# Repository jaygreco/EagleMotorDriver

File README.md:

EagleMotorDriver
================

The eagle filesizzles for the motor drizzle.

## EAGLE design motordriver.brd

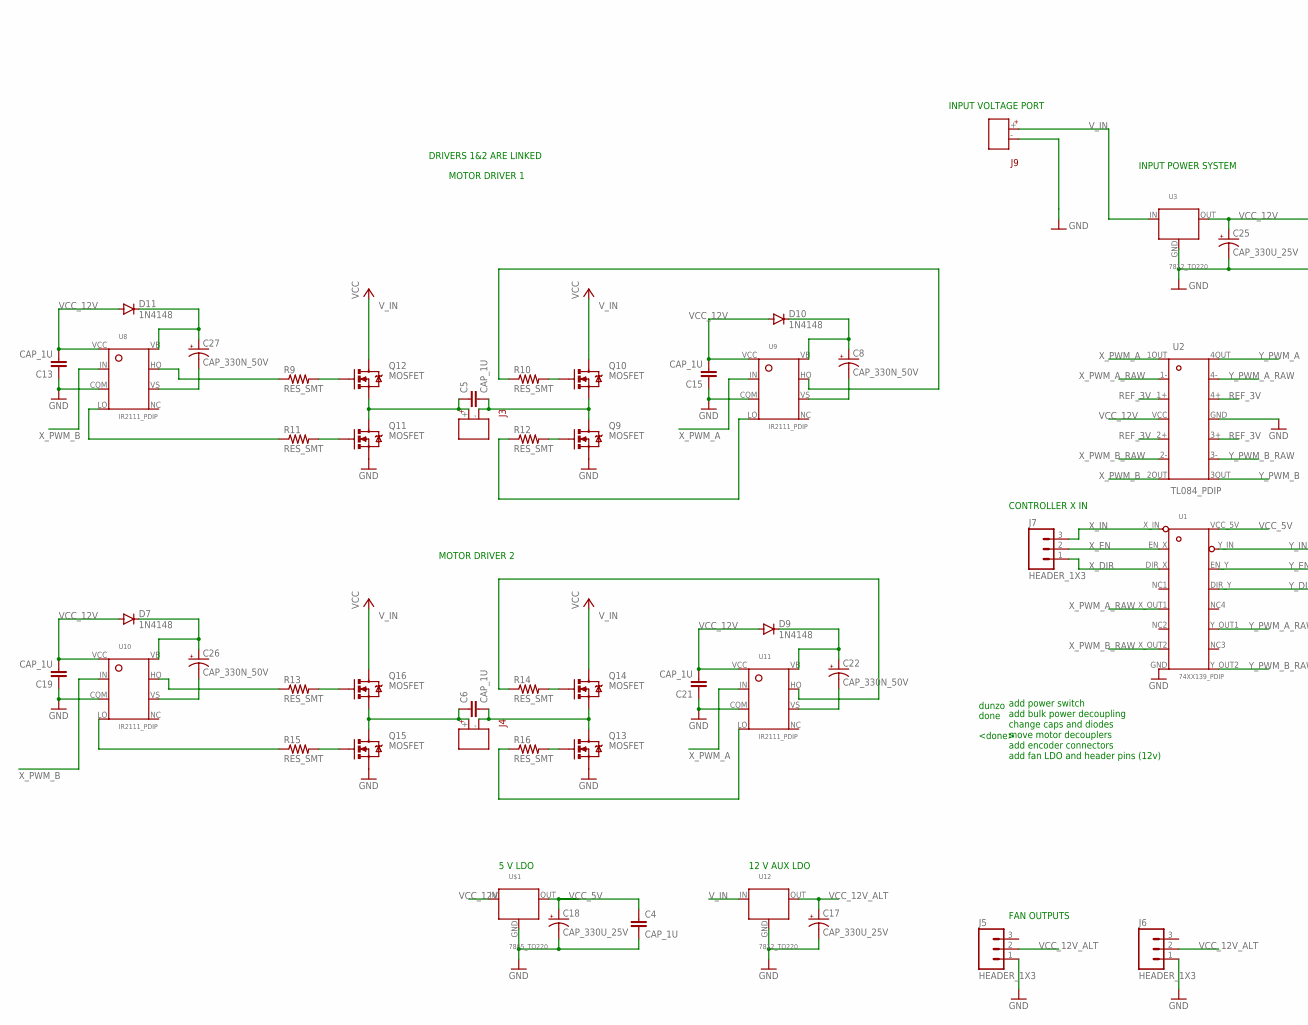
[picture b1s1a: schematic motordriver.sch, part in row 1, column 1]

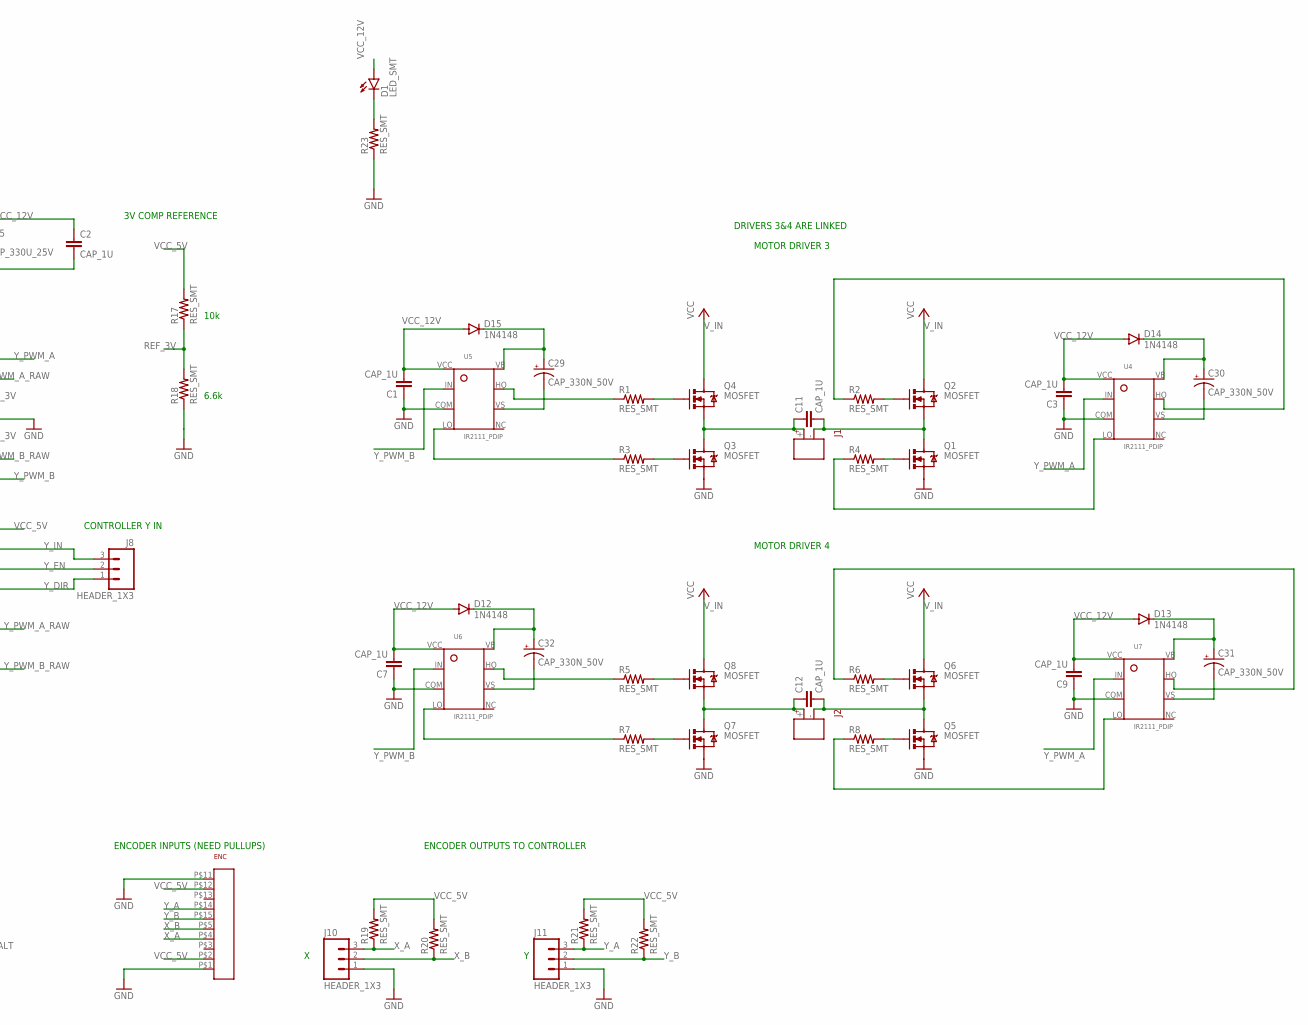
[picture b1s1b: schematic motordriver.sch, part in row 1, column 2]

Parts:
C1, C2, C3, C4, C5, C6, C7, C9, C11, C12, C13, C15, C19, C21: CAP_1U; 2DIP
C8, C22, C26, C27, C29, C30, C31, C32: CAP_330N_50V; RADIAL_5
C17, C18, C25: CAP_330U_25V; RADIAL_1O
D1: LED_SMT; LED_0603
D7, D9, D10, D11, D12, D13, D14, D15: 1N4148
ENC: CONN_5X2
J1, J2, J3, J4, J9: CONNECTOR_MOTORS; CONN_MOTOR
J5, J6, J7, J8, J10, J11: HEADER_1X3
Q1, Q2, Q3, Q4, Q5, Q6, Q7, Q8, Q9, Q10, Q11, Q12, Q13, Q14, Q15, Q16: MOSFET
R1, R2, R3, R4, R5, R6, R7, R8, R9, R10, R11, R12, R13, R14, R15, R16, R17, R18, R19, R20, R21, R22, R23: RES_SMT; 0603
U1: 74XX139_PDIP; 16PDIP
U2: TL084_PDIP; 14PDIP
U3, U12: 7812_TO220; TO-220
U4, U5, U6, U7, U8, U9, U10, U11: IR2111_PDIP; 8PDIP
U$1: 7805_TO220; TO-220

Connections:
GND_32: C1.P$1 (1), C2.P$2 (2), C3.P$1 (1), C4.P$2 (2), C7.P$1 (1), C9.P$1 (1), C13.P$1 (1), C15.P$1 (1), C17.-, C18.-, C19.P$1 (1), C21.P$1 (1), C25.-, ENC.P$1, ENC.P$11, J5.1, J6.1, J9.-, J10.1, J11.1, Q1.S, Q3.S, Q5.S, Q7.S, Q9.S, Q11.S, Q13.S, Q15.S, R18.1, R23.1, U1.GND, U2.GND, U3.GND, U4.COM, U5.COM, U6.COM, U7.COM, U8.COM, U9.COM, U10.COM, U11.COM, U12.GND, U$1.GND
unnamed: R12.1, U9.LO
unnamed: R8.1, U7.LO
unnamed: R10.1, U9.HO
unnamed: D1.C, R23.2
unnamed: R15.1, U10.LO
unnamed: C29.+, D15.C, U5.VB
unnamed: Q1.G, R4.2
unnamed: C29.-, U5.VS
unnamed: R1.1, U5.HO
unnamed: Q4.G, R1.2
unnamed: C11.P$1 (1), J1.+, Q3.D, Q4.S
unnamed: R4.1, U4.LO
unnamed: R3.1, U5.LO
unnamed: C11.P$2 (2), J1.-, Q1.D, Q2.S
unnamed: Q3.G, R3.2
unnamed: Q2.G, R2.2
unnamed: C30.+, D14.C, U4.VB
unnamed: C30.-, U4.VS
unnamed: R2.1, U4.HO
unnamed: R9.1, U8.HO
unnamed: R11.1, U8.LO
unnamed: C32.+, D12.C, U6.VB
unnamed: C32.-, U6.VS
unnamed: R5.1, U6.HO
unnamed: Q8.G, R5.2
unnamed: C12.P$1 (1), J2.+, Q7.D, Q8.S
unnamed: Q5.G, R8.2
unnamed: C12.P$2 (2), J2.-, Q5.D, Q6.S
unnamed: C31.+, D13.C, U7.VB
unnamed: C31.-, U7.VS
unnamed: R6.1, U7.HO
unnamed: R7.1, U6.LO
unnamed: Q7.G, R7.2
unnamed: Q6.G, R6.2
unnamed: R16.1, U11.LO
unnamed: Q13.G, R16.2
unnamed: C27.+, D11.C, U8.VB
unnamed: C27.-, U8.VS
unnamed: Q9.G, R12.2
unnamed: Q12.G, R9.2
unnamed: C5.P$1 (1), J3.+, Q11.D, Q12.S
unnamed: C5.P$2 (2), J3.-, Q9.D, Q10.S
unnamed: C8.+, D10.C, U9.VB
unnamed: C8.-, U9.VS
unnamed: Q11.G, R11.2
unnamed: Q10.G, R10.2
unnamed: C26.+, D7.C, U10.VB
unnamed: C26.-, U10.VS
unnamed: R13.1, U10.HO
unnamed: Q16.G, R13.2
unnamed: C6.P$1 (1), J4.+, Q15.D, Q16.S
unnamed: C6.P$2 (2), J4.-, Q13.D, Q14.S
unnamed: C22.+, D9.C, U11.VB
unnamed: C22.-, U11.VS
unnamed: R14.1, U11.HO
unnamed: Q15.G, R15.2
unnamed: Q14.G, R14.2
REF_3V: R17.1, R18.2, U2.1+, U2.2+, U2.3+, U2.4+
VCC_5V: C4.P$1 (1), C18.+, ENC.P$2, ENC.P$12, R17.2, R19.2, R20.2, R21.2, R22.2, U1.VCC_5V, U$1.OUT
VCC_12V: C1.P$2 (2), C2.P$1 (1), C3.P$2 (2), C7.P$2 (2), C9.P$2 (2), C13.P$2 (2), C15.P$2 (2), C19.P$2 (2), C21.P$2 (2), C25.+, D1.A, D7.A, D9.A, D10.A, D11.A, D12.A, D13.A, D14.A, D15.A, U2.VCC, U3.OUT, U4.VCC, U5.VCC, U6.VCC, U7.VCC, U8.VCC, U9.VCC, U10.VCC, U11.VCC, U$1.IN
VCC_12V_ALT: C17.+, J5.2, J6.2, U12.OUT
V_IN: J9.+, Q2.D, Q4.D, Q6.D, Q8.D, Q10.D, Q12.D, Q14.D, Q16.D, U3.IN, U12.IN
X_A: ENC.P$4, J10.3, R19.1
X_B: ENC.P$5, J10.2, R20.1
X_DIR: J7.1, U1.DIR_X
X_EN: J7.2, U1.EN_X
X_IN: J7.3, U1.X_IN
X_PWM_A: U2.1OUT (OUT1), U9.IN, U11.IN
X_PWM_A_RAW: U1.X_OUT1, U2.1-
X_PWM_B: U2.2OUT (OUT2), U8.IN, U10.IN
X_PWM_B_RAW: U1.X_OUT2, U2.2-
Y_A: ENC.P$14, J11.3, R21.1
Y_B: ENC.P$15, J11.2, R22.1
Y_DIR: J8.1, U1.DIR_Y
Y_EN: J8.2, U1.EN_Y
Y_IN: J8.3, U1.Y_IN
Y_PWM_A: U2.4OUT (OUT4), U4.IN, U7.IN
Y_PWM_A_RAW: U1.Y_OUT1, U2.4-
Y_PWM_B: U2.3OUT (OUT3), U5.IN, U6.IN
Y_PWM_B_RAW: U1.Y_OUT2, U2.3-

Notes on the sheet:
add power switch add bulk power decoupling change caps and diodes move motor decouplers add encoder connectors add fan LDO and header pins (12v)
<done>
dunzo
done
5 V LDO
12 V AUX LDO
CONTROLLER X IN
CONTROLLER Y IN
MOTOR DRIVER 1
MOTOR DRIVER 2
MOTOR DRIVER 3
MOTOR DRIVER 4
ENCODER INPUTS (NEED PULLUPS)
INPUT POWER SYSTEM
3V COMP REFERENCE
DRIVERS 1&2 ARE LINKED
DRIVERS 3&4 ARE LINKED
10k
6.6k
INPUT VOLTAGE PORT
FAN OUTPUTS
ENCODER OUTPUTS TO CONTROLLER

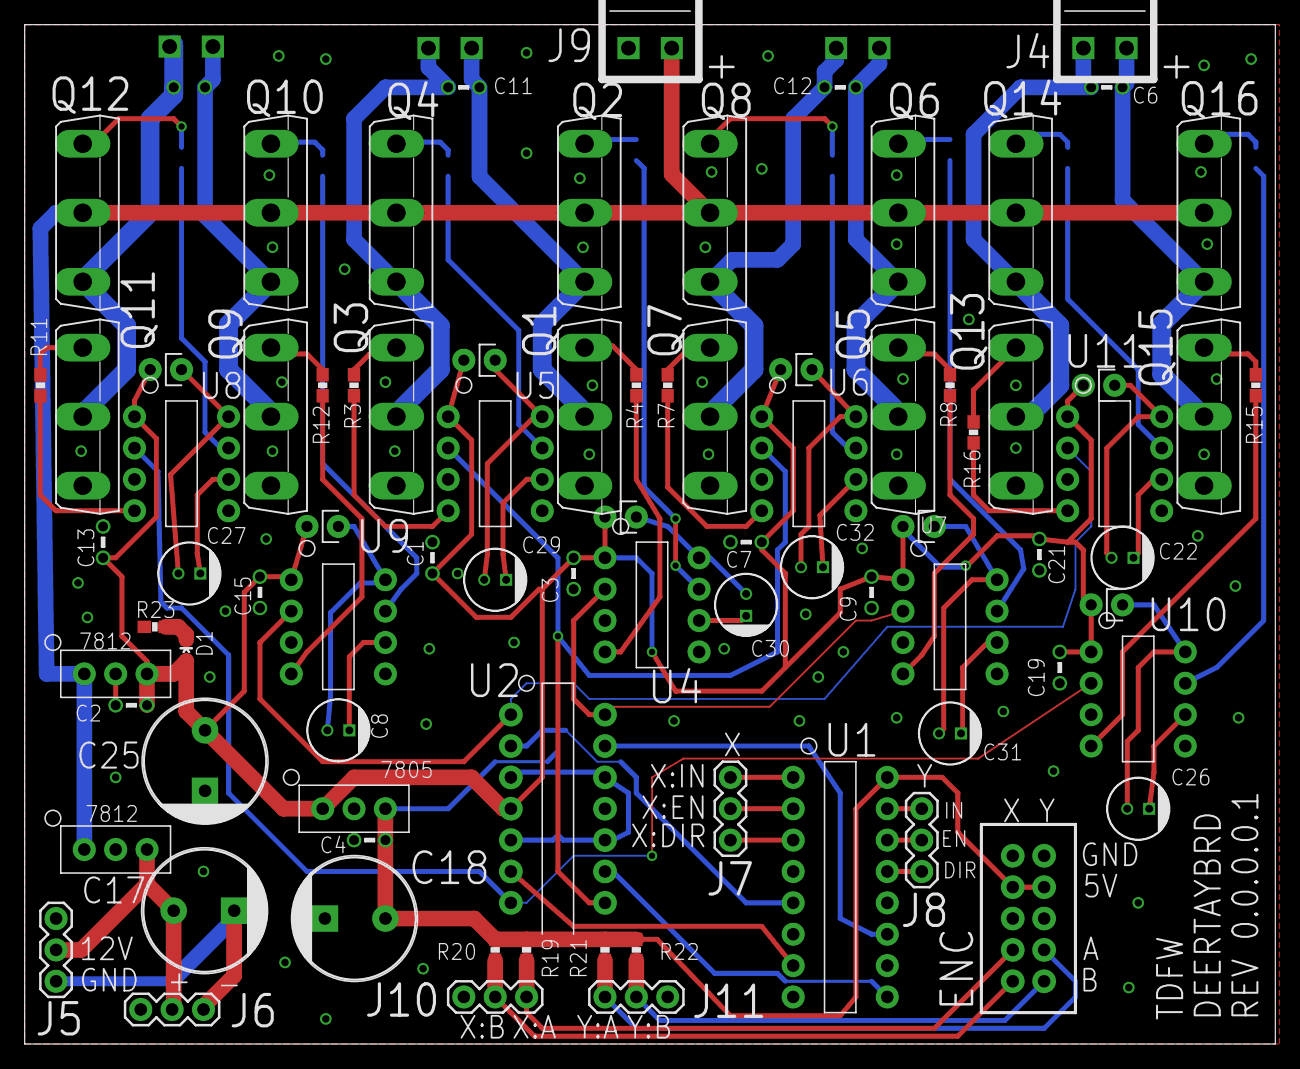
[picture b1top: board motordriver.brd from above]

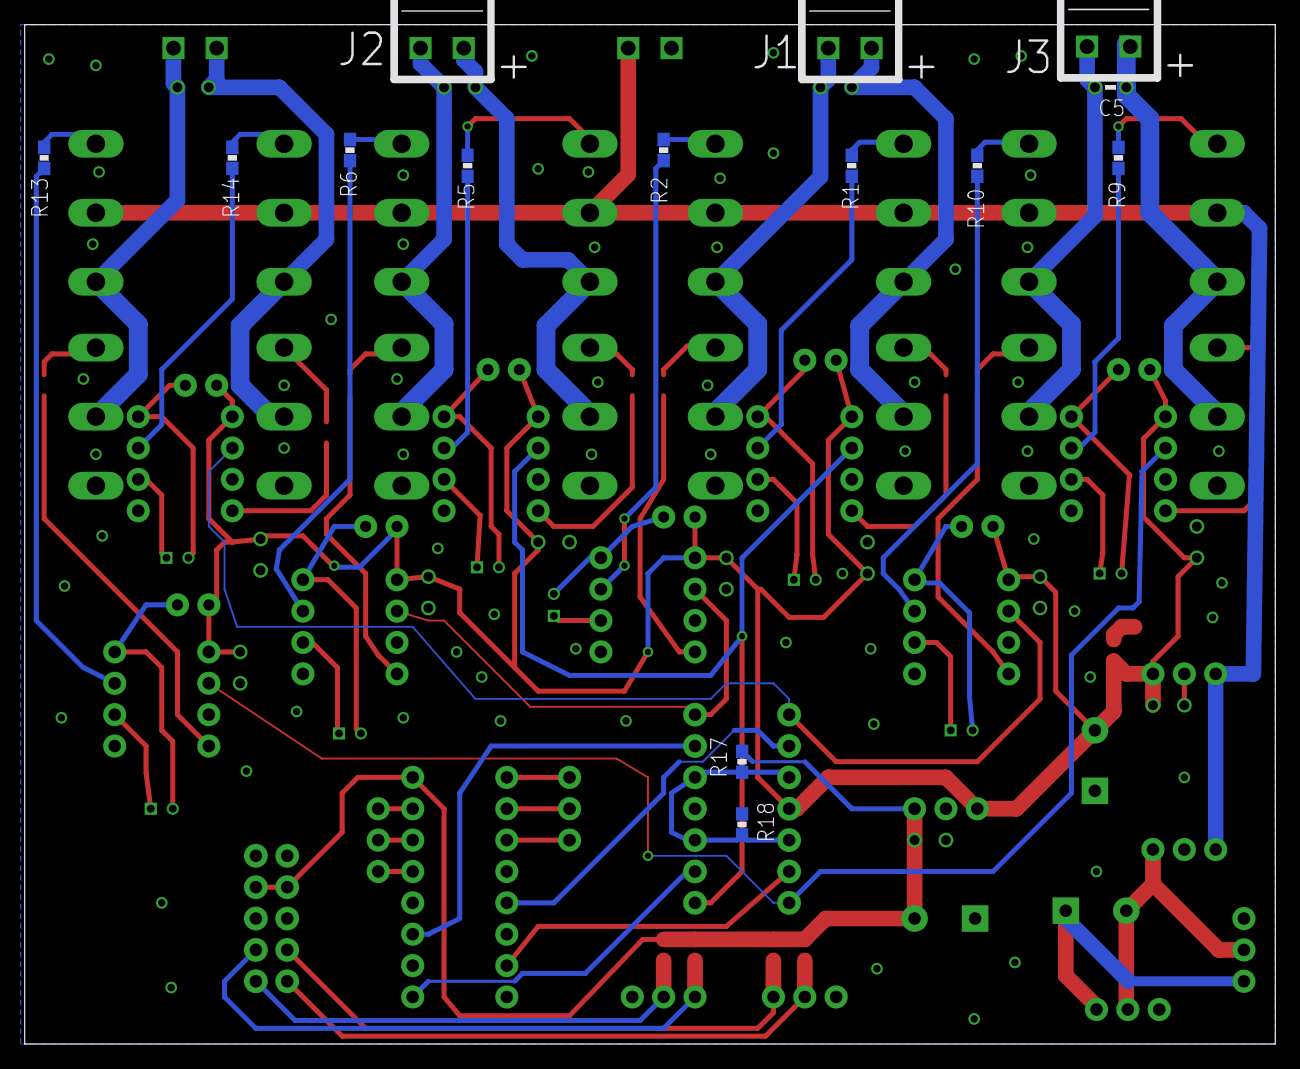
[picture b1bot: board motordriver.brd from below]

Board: 2 copper layers, 101.3 x 82.5 mm, 98 parts (14 on the bottom side), 81 nets.

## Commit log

2014-12-19 Added library file.
2014-12-19 Added new parts
2015-01-02 Added more symbols.
2015-01-02 Changed schematic
    Suck it.
2015-01-02 Testing the save function
    Dicks
2015-01-02 Initial schat
2015-01-03 Basic completed driver Schematic
    Need the Dode, 5v LDO, and miscellaneous connector footprints
2015-01-13 Added more symbols.
    Diode, connectors, and small polcap
2015-01-13 Added header pins.
2015-01-13 Changed schematic
2015-01-15 Schematic changes
    Added power switch, power decoups, moter decoups, fan connections
2015-01-15 FIXED STUFF
2015-01-15 Changed mistakes...
    Oh god
2015-01-20 Finished schematic
2015-01-20 readmizzle
2015-01-20 HumDdunm
    slight changes
2015-01-22 Fixed cap layouts
2015-01-22 Created board.
2015-01-22 Added PCB
    Motor driver movie film for theaters part II
2015-01-25 Arranged H-bridge components
    Looks like there will be enough space to fit the essential admin
    components
2015-01-25 Cap23 just got murde
    I put it in the dirt or somethin
2015-01-29 Updated diode model
2015-01-29 Revert "Updated diode model"
    This reverts commit 0289d321ace38622cd90e5d7b8b2b2eedb9a8107.
2015-01-29 double fixed dodes
2015-01-29 More PCB tinkering
    Routing will commence soon
2015-02-02 Dank
    ass
2015-02-02 PCB Layout Overhaul
    Reworked H-Bridge, this time it will be possible to route VCC(24v)
    without killing yourself.
    Couple clearance issues that need to be cleared before I proceed.
2015-02-02 Components arranged, 86'ed the 36V cap (fit ext.)
    YEEEEEHAA it all fits. I will still be rearranging components, but
    initially they all fit. Routing will happen later this afternoon.
2015-02-03 Routing Adventure Part I
    Its never ogre.
2015-02-03 PCB Routing the Trilogy Part II
    SO MUCH TO DO SO MUCH TO SEE
2015-02-03 TIS FUCKING DONE
2015-02-03 PCB sweep up, Part III of the 8 part Penilogy
    Yeah
2015-02-03 Added design rule
2015-02-03 SHIP IT!
2015-02-03 Front side labels...COMPLETE
    IT tAkes AlOT of COoKs to mAke A STew.
2015-02-03 Final Design, SHIPPED
    Complete
2015-02-03 added cam file
2015-02-03 Added the Gerber files
    Groovy
2015-03-22 Added final screenshots and picture of PCB
